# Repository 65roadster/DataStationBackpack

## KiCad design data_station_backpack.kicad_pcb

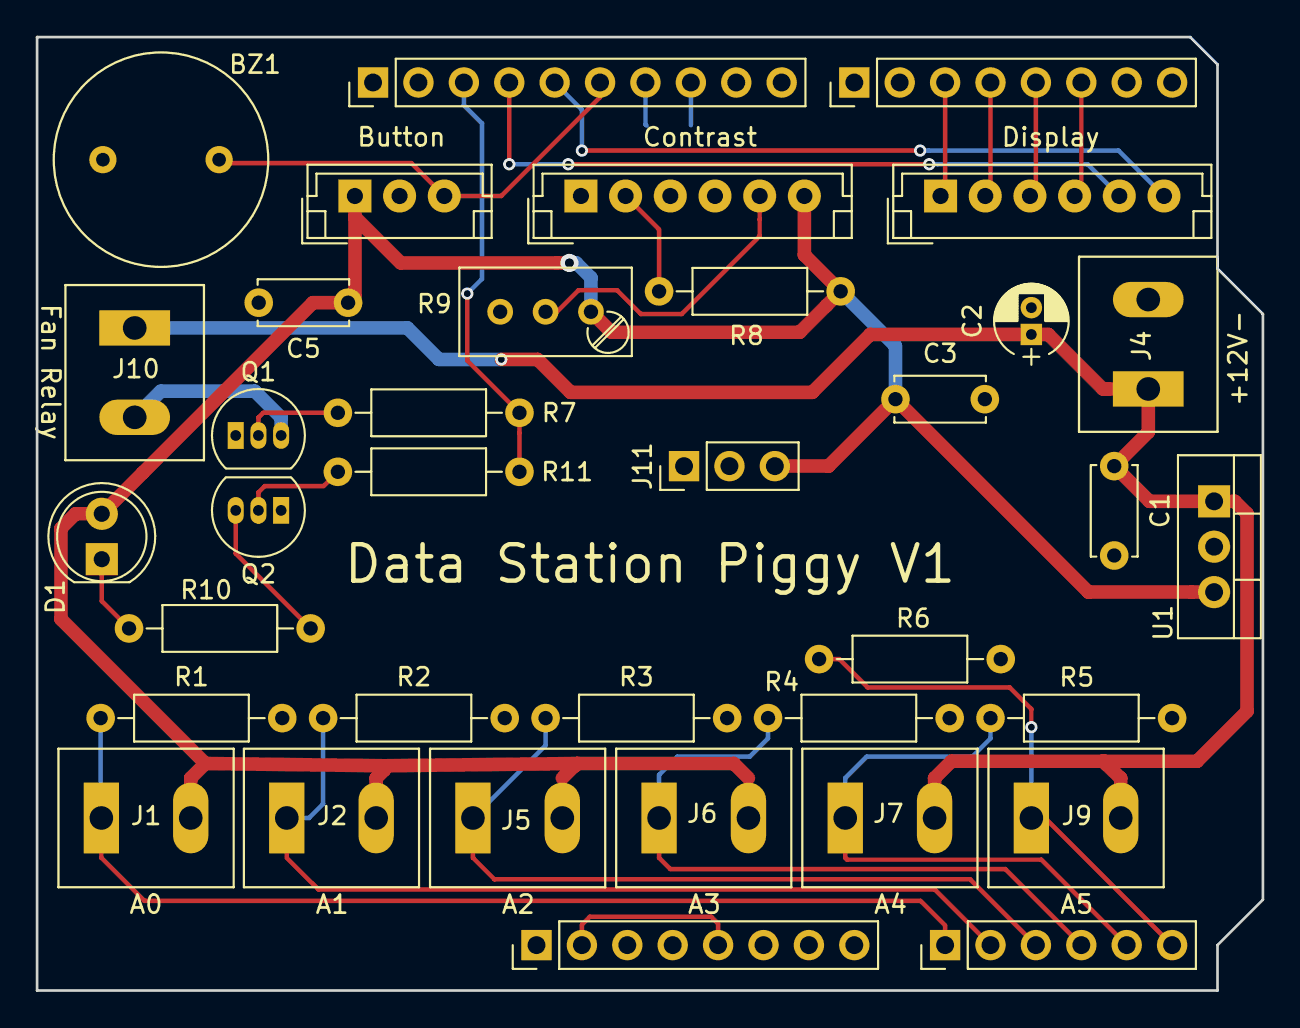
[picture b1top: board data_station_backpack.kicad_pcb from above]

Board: 2 copper layers, 68.6 x 53.3 mm, 37 parts (1 on the bottom side), 26 nets.

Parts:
BZ1: Buzzer; Buzzer-WT-1212
C1: 0.33; C_Disc_D5.0mm_W2.5mm_P5.00mm
C2: 10u; CP_Radial_D4.0mm_P1.50mm
C3, C5: 0.1; C_Disc_D5.0mm_W2.5mm_P5.00mm
C6: 0.1; C_0805_HandSoldering
D1: LED; LED_D5.0mm
J1, J2, J4, J5, J6, J7, J9, J10: Conn_01x02_Male; Ryans_Terminal_Block_10mm7.75mmP5mm
J3, J8: Conn_01x06_Male; JST_EH_B06B-EH-A_06x2.50mm_Straight
J11: Conn_01x03_Male; Pin_Header_Straight_1x03_Pitch2.54mm
J12: Conn_01x06_Male; JST_EH_B03B-EH-A_03x2.50mm_Straight
J13: Conn_01x06_Male; Pin_Header_Straight_1x06_Pitch2.54mm
J14, J16: Conn_01x08_Male; Pin_Header_Straight_1x08_Pitch2.54mm
J17: Conn_01x10_Male; Pin_Header_Straight_1x10_Pitch2.54mm
Q1, Q2: 2N2222; TO-92_Inline_Narrow_Oval
R1, R2, R3, R4: 10k; R_Axial_DIN0207_L6.3mm_D2.5mm_P10.16mm_Horizontal
R5, R6, R8, R10: 220; R_Axial_DIN0207_L6.3mm_D2.5mm_P10.16mm_Horizontal
R7: 2.2k; R_Axial_DIN0207_L6.3mm_D2.5mm_P10.16mm_Horizontal
R9: 10k; Potentiometer_Trimmer_Bourns_3296W
R11: 4.7k; R_Axial_DIN0207_L6.3mm_D2.5mm_P10.16mm_Horizontal
U1: LM7805_TO220; TO-220-3_Vertical

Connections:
5V: J14.2, J14.5
+5V: C3.1, C5.1, D1.2, J1.2, J2.2, J3.6, J5.2, J6.2, J11.3, J12.1, R8.2, R9.1, U1.3
+12V: C1.1, C2.1, J4.1, J7.2, J9.2, J10.1, U1.1
A0: J1.1, J13.1, R1.1
A1: J2.1, J13.2, R2.1
A2: J5.1, J13.3, R3.1
A3: J6.1, J13.4, R4.1
A4: J7.1, J13.5, R5.1
A5: J9.1, J13.6, R6.1
AREF: C6.1, J17.8
D2: J8.1, J16.3
D3: J8.2, J16.4
D4: J8.3, J16.5
D5: J8.4, J16.6
D10: J17.3, R7.2, R11.2
D11: J8.5, J17.4
D12: J8.6, J17.5
D13: BZ1.1, J12.3, J17.6
GND: BZ1.2, C1.2, C2.2, C3.2, C5.2, C6.2, J3.1, J3.3, J3.4, J4.2, J11.1, J11.2, J12.2, J14.6, J14.7, J17.7, Q1.1, Q2.1, R1.2, R2.2, R3.2, R4.2, R5.2, R6.2, R9.3, U1.2
unnamed: D1.1, R10.2
unnamed: J3.2, R8.1
unnamed: J3.5, R9.2
unnamed: J10.2, Q1.3
unnamed: Q1.2, R7.1
unnamed: Q2.2, R11.1
unnamed: Q2.3, R10.1

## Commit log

2020-01-19 Updated to reflect actual order
